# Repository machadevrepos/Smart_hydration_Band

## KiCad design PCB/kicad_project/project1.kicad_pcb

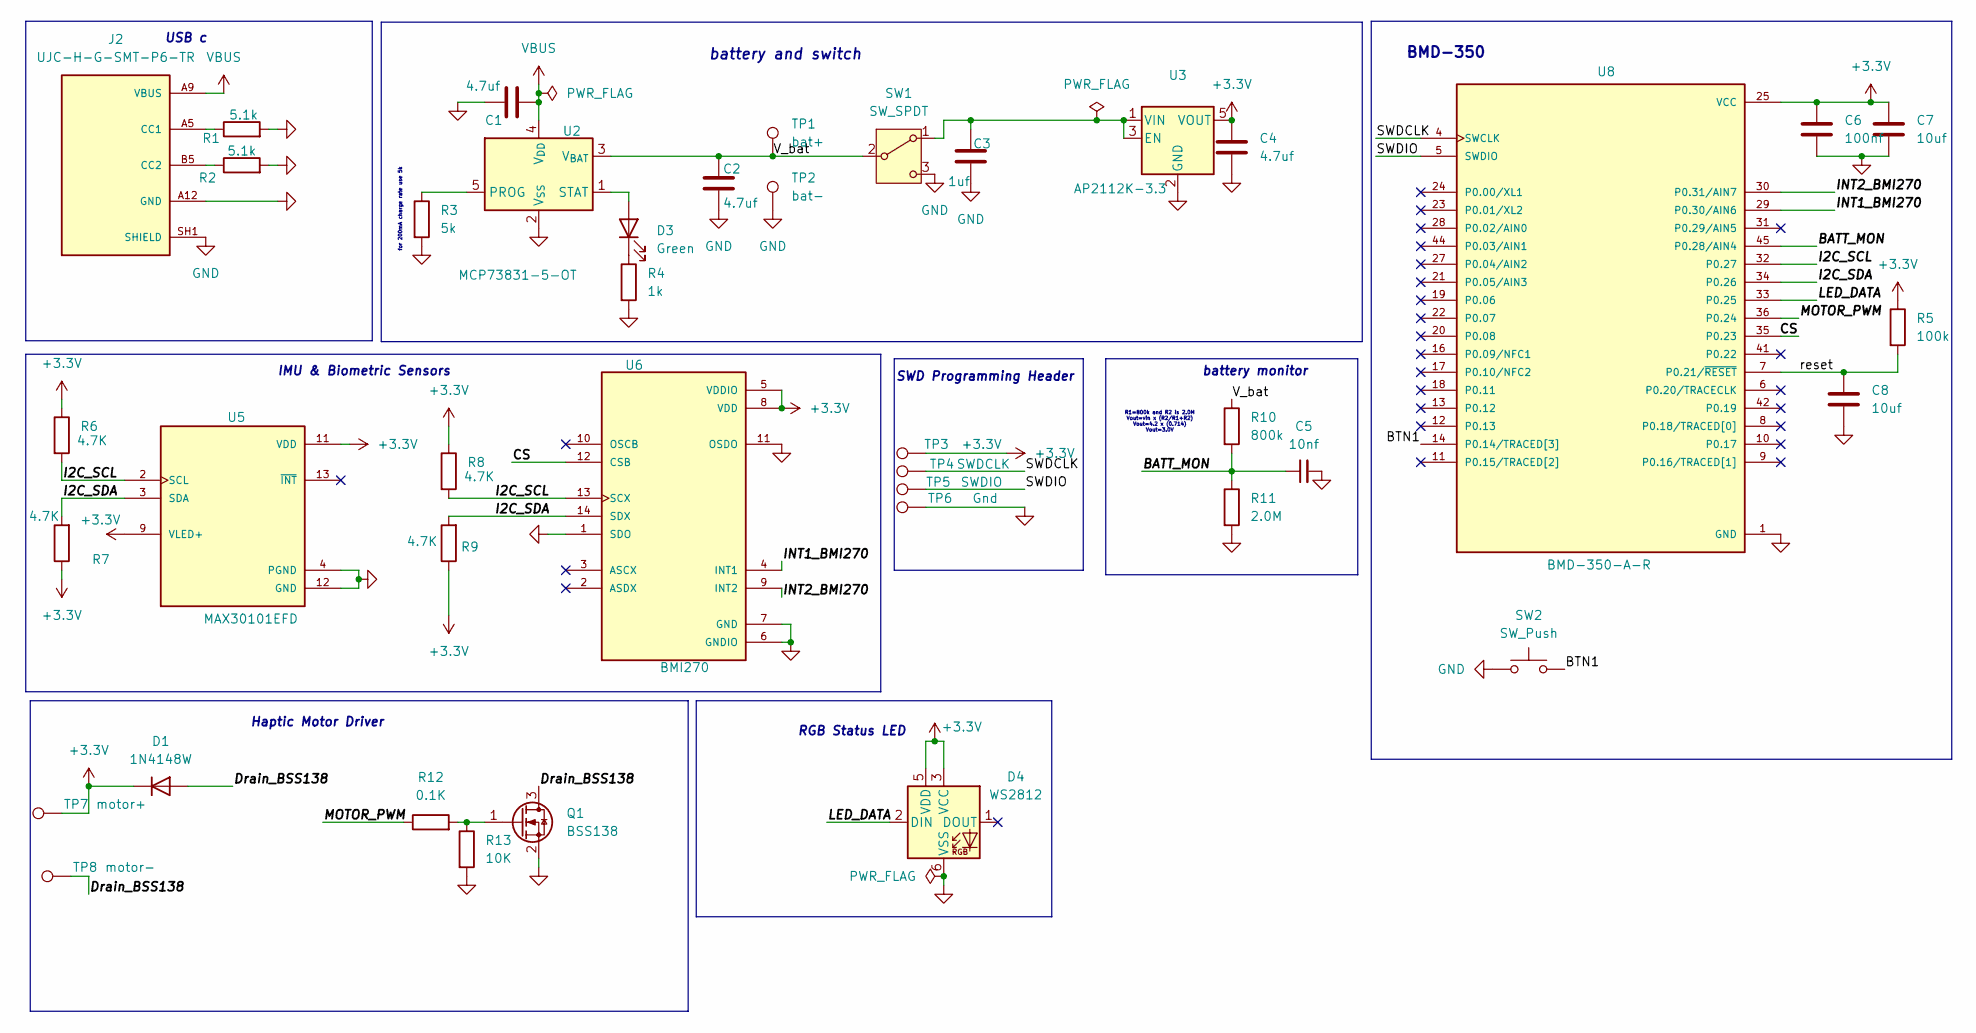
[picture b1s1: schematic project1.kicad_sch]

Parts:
C1, C2, C4: 4.7uf; C_0402_1005Metric
C3: 1uf; C_0402_1005Metric
C5: 10nf; C_0402_1005Metric
C6: 100nf; C_0402_1005Metric
C7, C8: 10uf; C_0402_1005Metric
D1: 1N4148W; D_SOD-123
D3: Green; LED_0402_1005Metric
D4: WS2812; LED_WS2812_PLCC6_5.0x5.0mm_P1.6mm
J2: UJC-H-G-SMT-P6-TR; SAMESKY_UJC-H-G-SMT-P6-TR; PARTREV 1.0
Q1: BSS138; SOT-23
R1, R2: 5.1k; R_0402_1005Metric
R3: 5k; R_0402_1005Metric
R4: 1k; R_0402_1005Metric
R5: 100k; R_0402_1005Metric
R6, R7, R8, R9: 4.7K; R_0402_1005Metric
R10: 800k; R_0402_1005Metric
R11: 2.0M; R_0402_1005Metric
R12: 0.1K; R_0402_1005Metric
R13: 10K; R_0402_1005Metric
SW1: SW_SPDT; SW_SPDT_PCM12
SW2: SW_Push; SW_Push_SPST_NO_Alps_SKRK
TP1: bat+; TestPoint_Pad_D1.0mm
TP2: bat-; TestPoint_Pad_D1.0mm
TP3: +3.3V; TestPoint_Pad_D1.0mm
TP4: SWDCLK; TestPoint_Pad_D1.0mm
TP5: SWDIO; TestPoint_Pad_D1.0mm
TP6: Gnd; TestPoint_Pad_D1.0mm
TP7: motor+; TestPoint_Pad_D1.0mm
TP8: motor-; TestPoint_Pad_D1.0mm
U2: MCP73831-5-OT; SOT-23-5
U3: AP2112K-3.3; SOT-23-5
U5: MAX30101EFD; Maxim_OLGA-14_3.3x5.6mm_P0.8mm; PARTREV 2
U6: BMI270; Bosch_LGA-14_3x2.5mm_P0.5mm
U8: BMD-350-A-R; XCVR_BMD-350-A-R; PARTREV 2.0

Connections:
+3.3V: C4.1, C6.1, C7.1, D1.1 (K), D4.3 (VCC), D4.5 (VDD), R5.1, R6.1, R7.1, R8.1, R9.1, TP3.1 (1_1), TP7.1 (1_1), U3.5 (VOUT), U5.9 (VLED+), U5.10 (VLED+), U5.11 (VDD), U6.5 (VDDIO), U6.8 (VDD), U8.25 (VCC)
/BATT_MON: C5.1, R10.2, R11.1, U8.45 (P0.28/AIN4)
/BTN1: SW2.2, U8.14 (P0.14/TRACED[3])
/CS: U6.12 (CSB), U8.35 (P0.23)
/Drain_BSS138: D1.2 (A), Q1.3 (D), TP8.1 (1_1)
/I2C_SCL: R6.2, R8.2, U5.2 (SCL), U6.13 (SCX), U8.32 (P0.27)
/I2C_SDA: R7.2, R9.2, U5.3 (SDA), U6.14 (SDX), U8.34 (P0.26)
/INT1_BMI270: U6.4 (INT1), U8.29 (P0.30/AIN6)
/INT2_BMI270: U6.9 (INT2), U8.30 (P0.31/AIN7)
/LED_DATA: D4.2 (DIN), U8.33 (P0.25)
/MOTOR_PWM: R12.1, U8.36 (P0.24)
/SWDCLK: TP4.1 (1_1), U8.4 (SWCLK)
/SWDIO: TP5.1 (1_1), U8.5 (SWDIO)
/V_bat: C2.1, R10.1, SW1.2 (B), TP1.1 (1_1), U2.3 (V_{BAT})
/reset: C8.1, R5.2, U8.7 (P0.21/~RESET)
GND: C1.1, C2.2, C3.2, C4.2, C5.2, C6.2, C7.2, C8.2, D4.6 (VSS), J2.A12 (GND), J2.B12 (GND), J2.SH1 (SHIELD), J2.SH2 (SHIELD), J2.SH3 (SHIELD), J2.SH4 (SHIELD), Q1.2 (S), R1.2, R2.2, R3.2, R4.2, R11.2, R13.2, SW1.3 (C), SW2.1, TP2.1 (1_1), TP6.1 (1_1), U2.2 (V_{SS}), U3.2 (GND), U5.4 (PGND), U5.12 (GND), U6.1 (SDO), U6.6 (GNDIO), U6.7 (GND), U6.11 (OSDO), U8.1 (GND), U8.2 (GND), U8.3 (GND), U8.15 (GND), U8.26 (GND), U8.37 (GND), U8.38 (GND), U8.39 (GND), U8.40 (GND), U8.43 (GND), U8.46 (GND), U8.47 (GND)
unnamed: D3.2 (A), U2.1 (STAT)
unnamed: D3.1 (K), R4.1
unnamed: J2.A5 (CC1), R1.1
unnamed: J2.B5 (CC2), R2.1
unnamed: Q1.1 (G), R12.2, R13.1
unnamed: C3.1, SW1.1 (A), U3.1 (VIN), U3.3 (EN)
unnamed: R3.1, U2.5 (PROG)
VBUS: C1.2, J2.A9 (VBUS), J2.B9 (VBUS), U2.4 (V_{DD})

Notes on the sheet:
USB c
RGB Status LED
battery monitor
SWD Programming Header
IMU & Biometric Sensors
R1=800k and R2 is 2.0M Vout=vin x (R2/R1+R2) Vout=4.2 x (0.714) Vout=3.0V
for 200mA charge rate use 5k
BMD-350
battery and switch
Haptic Motor Driver

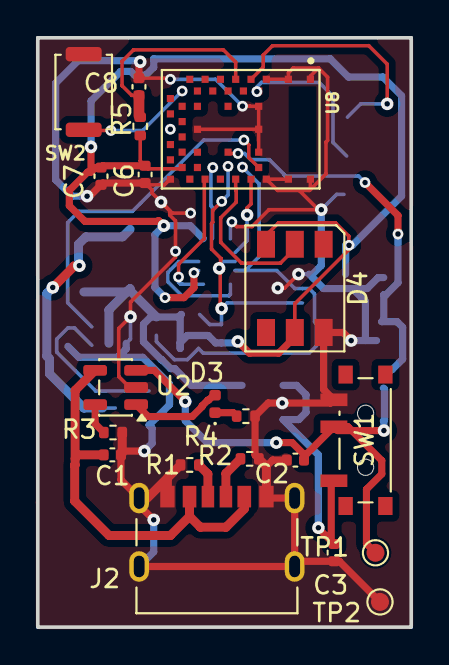
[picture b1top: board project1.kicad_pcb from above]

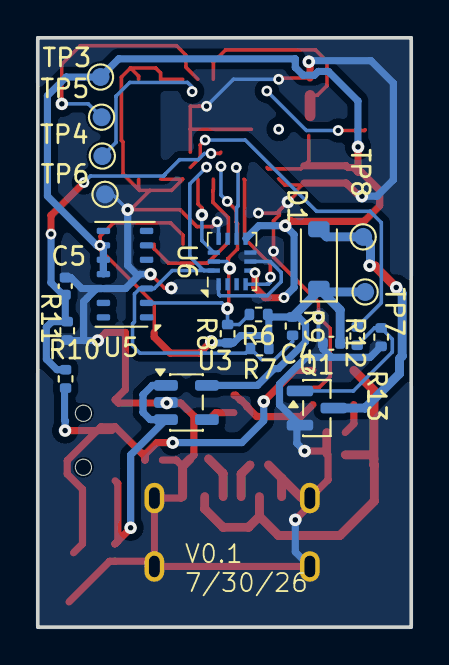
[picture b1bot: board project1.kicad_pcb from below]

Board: 2 copper layers, 20.7 x 32.7 mm, 41 parts (21 on the bottom side), 24 nets.
